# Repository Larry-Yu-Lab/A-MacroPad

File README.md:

# A-MacroPad
A customisable Macro Pad powered by the XIAO Seeed Studio RP2040, with a 3.5 inch screen and my own fully orginial PCB. 

HOW To USE:
This is a fully customisable macropad where you could do a lot of things! Customize each key to complete its own function and more.

Schematics: 

PCB Board Layout:

3D View:

The Case:

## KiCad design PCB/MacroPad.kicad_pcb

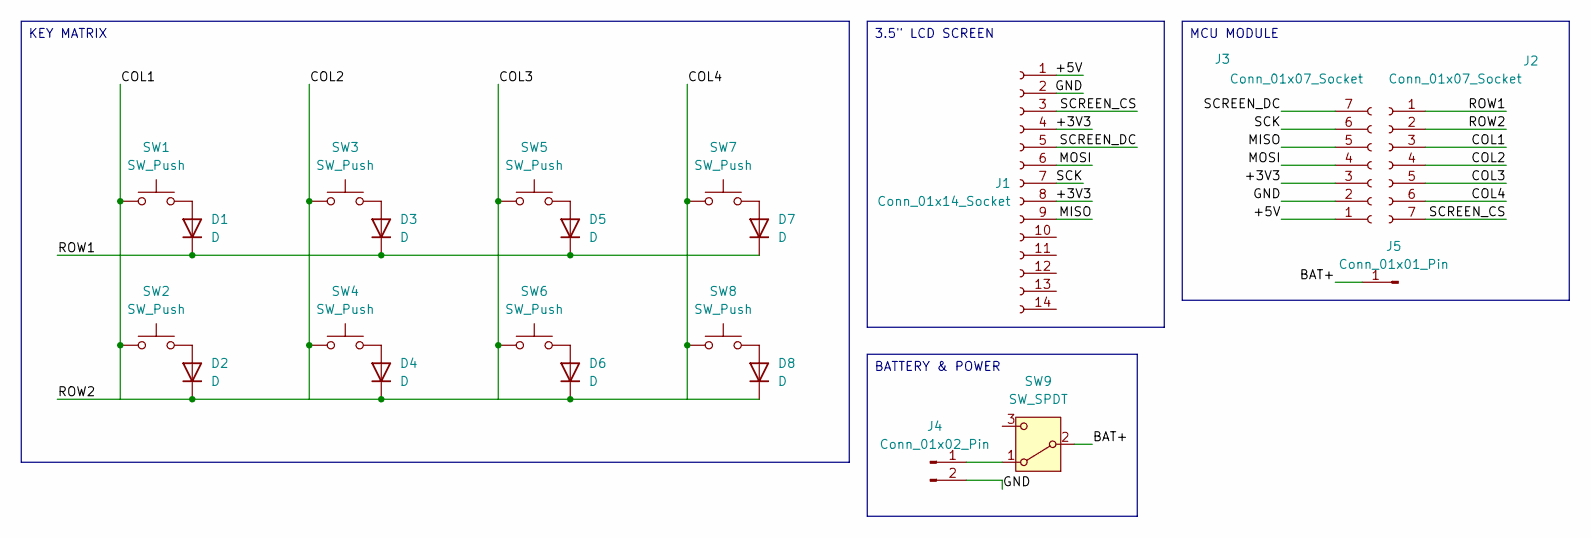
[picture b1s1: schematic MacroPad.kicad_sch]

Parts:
D1, D2, D3, D4, D5, D6, D7, D8: D; D_SOD-123
J1: Conn_01x14_Socket; PinHeader_1x14_P2.54mm_Vertical
J2, J3: Conn_01x07_Socket; PinHeader_1x07_P2.54mm_Vertical_SMD_Pin1Right
J4: Conn_01x02_Pin; JST_PH_S2B-PH-K_1x02_P2.00mm_Horizontal
J5: Conn_01x01_Pin; PinHeader_1x01_P1.00mm_Horizontal
SW1, SW2, SW3, SW4, SW5, SW6, SW7, SW8: SW_Push; SW_Cherry_MX_1.00u_PCB
SW9: SW_SPDT; SW_DPDT_CK_JS202011JCQN

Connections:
/+3V3: J1.4, J1.8, J3.3
/+5V: J1.1, J3.1
/BAT+: J5.1 (Pin_1_1), SW9.2 (B)
/COL1: J2.3, SW1.1, SW2.1
/COL2: J2.4, SW3.1, SW4.1
/COL3: J2.5, SW5.1, SW6.1
/COL4: J2.6, SW7.1, SW8.1
/GND: J1.2, J3.2, J4.2
/MISO: J1.9, J3.5
/MOSI: J1.6, J3.4
/ROW1: D1.1 (K), D3.1 (K), D5.1 (K), D7.1 (K), J2.1
/ROW2: D2.1 (K), D4.1 (K), D6.1 (K), D8.1 (K), J2.2
/SCK: J1.7, J3.6
/SCREEN_CS: J1.3, J2.7
/SCREEN_DC: J1.5, J3.7
unnamed: D1.2 (A), SW1.2
unnamed: D2.2 (A), SW2.2
unnamed: D3.2 (A), SW3.2
unnamed: D4.2 (A), SW4.2
unnamed: D5.2 (A), SW5.2
unnamed: D6.2 (A), SW6.2
unnamed: D7.2 (A), SW7.2
unnamed: D8.2 (A), SW8.2
unnamed: J4.1, SW9.1 (A)

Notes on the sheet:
BATTERY & POWER
MCU MODULE
3.5" LCD SCREEN
KEY MATRIX

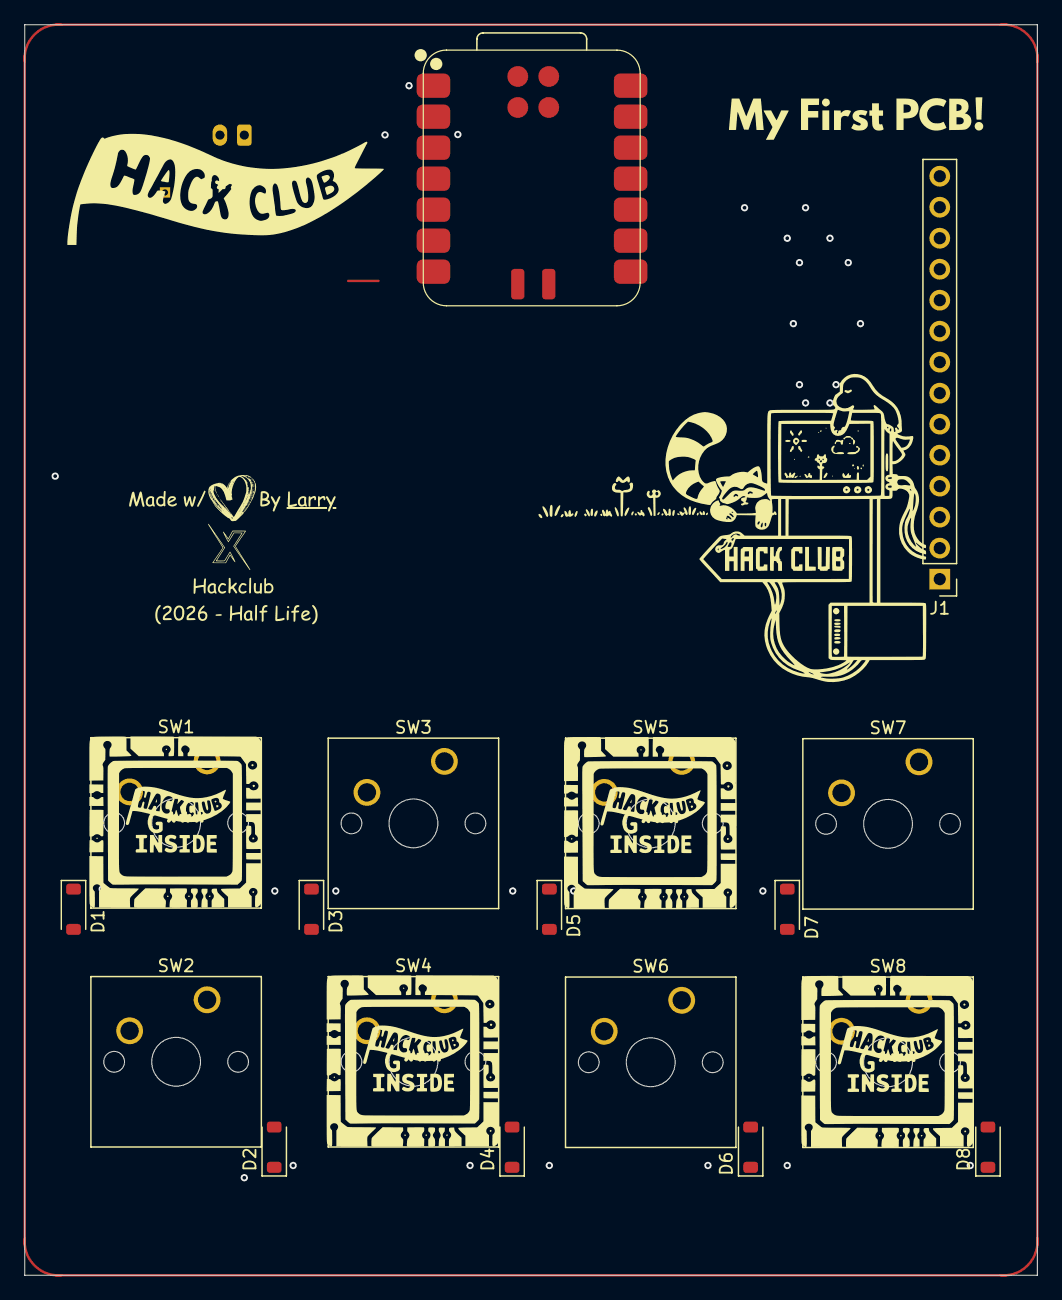
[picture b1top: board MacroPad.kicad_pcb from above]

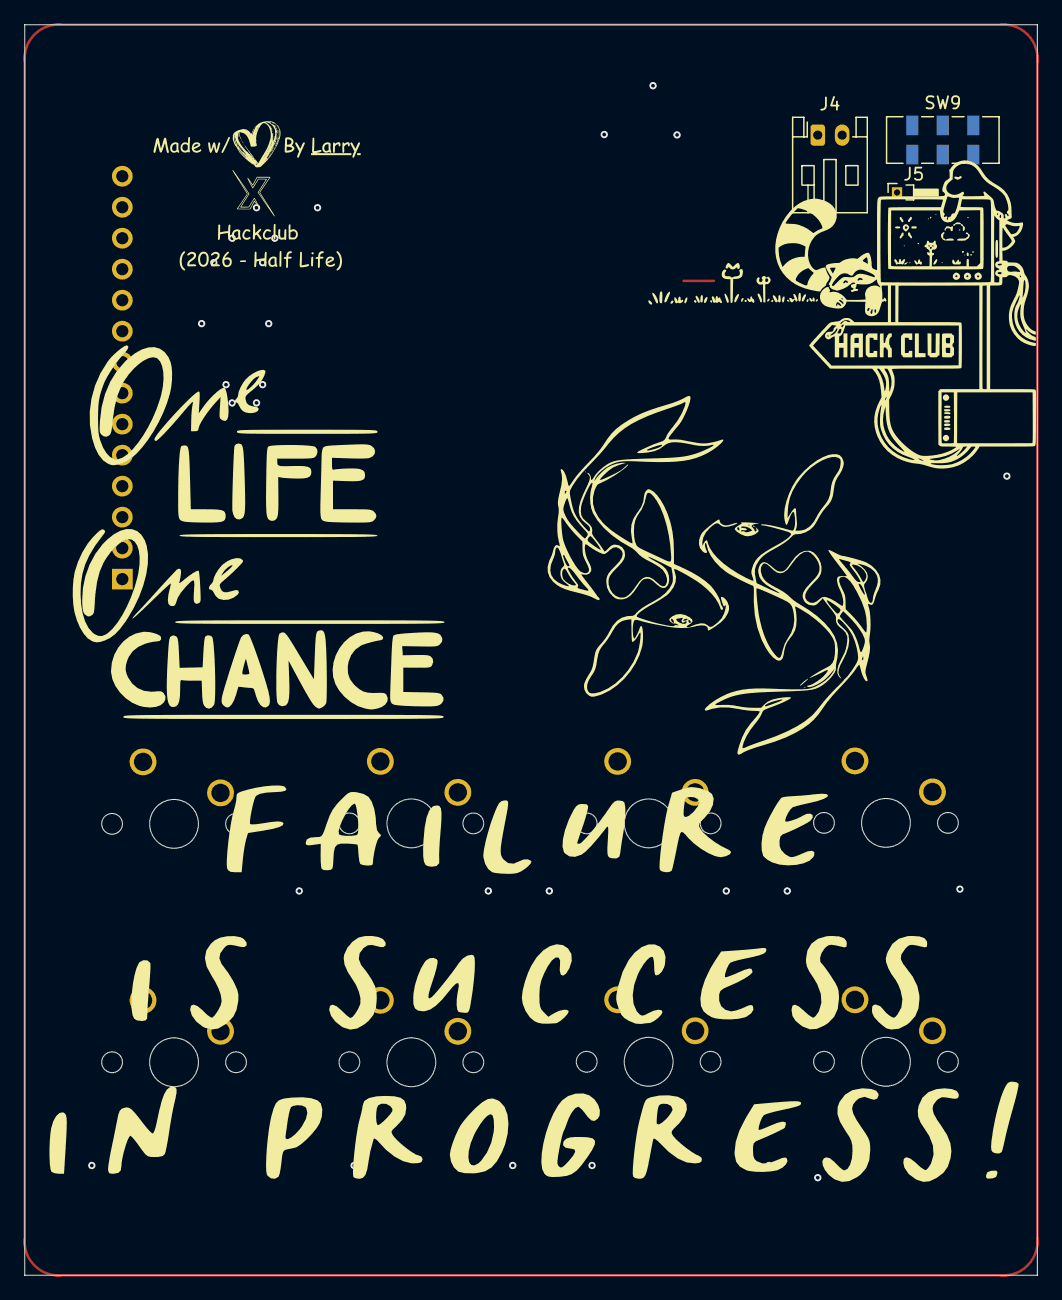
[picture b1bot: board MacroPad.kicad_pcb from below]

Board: 2 copper layers, 83.0 x 102.5 mm, 20 parts (3 on the bottom side), 18 nets.
